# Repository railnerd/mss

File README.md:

Modular Signal System Boards
Copyright (c) 2012, Silicon Valley Lines Model Railroad Club

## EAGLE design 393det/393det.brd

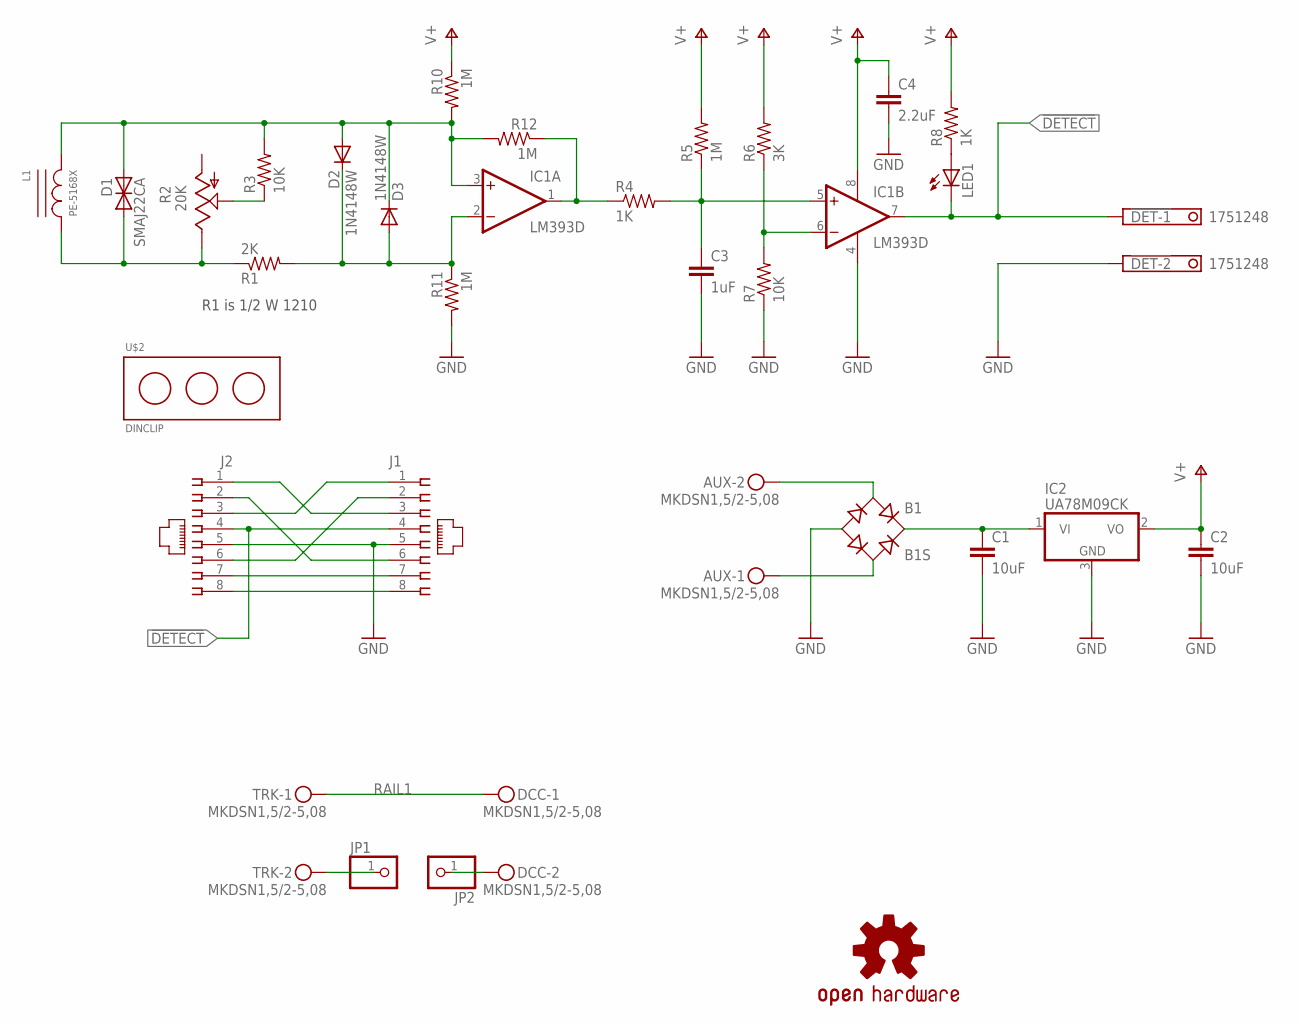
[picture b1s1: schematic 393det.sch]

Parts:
!DET: 1751248
AUX: MKDSN1,5/2-5,08
B1: B1S; MBS
C1, C2: 10uF; 1210
C3: 1uF; 0805
C4: 2.2uF; 0805
D1: SMAJ22CA; SMA
D2, D3: 1N4148W; SOD123
DCC: MKDSN1,5/2-5,08
IC1: LM393D; SO08
IC2: UA78M09CK; TO252
J1, J2: 215877-7
JP1, JP2: PINHD-1X1; 1X01
L1: PE-5168X
LED1: LED5MM
R1: 2K; R1206
R2: 20K; B25U
R3, R7: 10K; 0805
R4, R8: 1K; 0805
R5, R10, R11, R12: 1M; 0805
R6: 3K; 0805
TRK: MKDSN1,5/2-5,08
U$1: OSHW-LOGOM; OSHW-LOGO-M
U$2: DINCLIP; 1201578

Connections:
!DETECT: !DET.1, IC1.7 (OUT), J1.4, J2.4, LED1.K (C)
GND: !DET.2, B1.-, C1.2, C2.2, C3.2, C4.2, IC1.4 (V-), IC2.3 (GND), J1.5, J2.5, R7.1, R11.2
unnamed: D1.A (1), D2.A, D3.C, IC1.3 (+IN), L1.P$2, R3.2, R10.2, R12.2
unnamed: C3.1, IC1.5 (+IN), R4.2, R5.1
unnamed: D2.C, D3.A, IC1.2 (-IN), R1.2, R11.1
unnamed: D1.C (2), L1.P$1, R1.1, R2.E
unnamed: R2.S, R3.1
unnamed: LED1.A, R8.1
unnamed: AUX.2, B1.AC1
unnamed: AUX.1, B1.AC2
unnamed: J1.8, J2.8
unnamed: JP1.1, TRK.2
unnamed: DCC.2, JP2.1
unnamed: J1.7, J2.7
unnamed: IC1.1 (OUT), R4.1, R12.1
unnamed: IC1.6 (-IN), R6.1, R7.2
unnamed: J1.3, J2.1
unnamed: J1.1, J2.3
unnamed: J1.6, J2.2
unnamed: J1.2, J2.6
unnamed: B1.+, C1.1, IC2.1 (VI)
RAIL1: DCC.1, TRK.1
V+: C2.1, C4.1, IC1.8 (V+), IC2.2 (VO), R5.2, R6.2, R8.2, R10.1

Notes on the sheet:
R1 is 1/2 W 1210

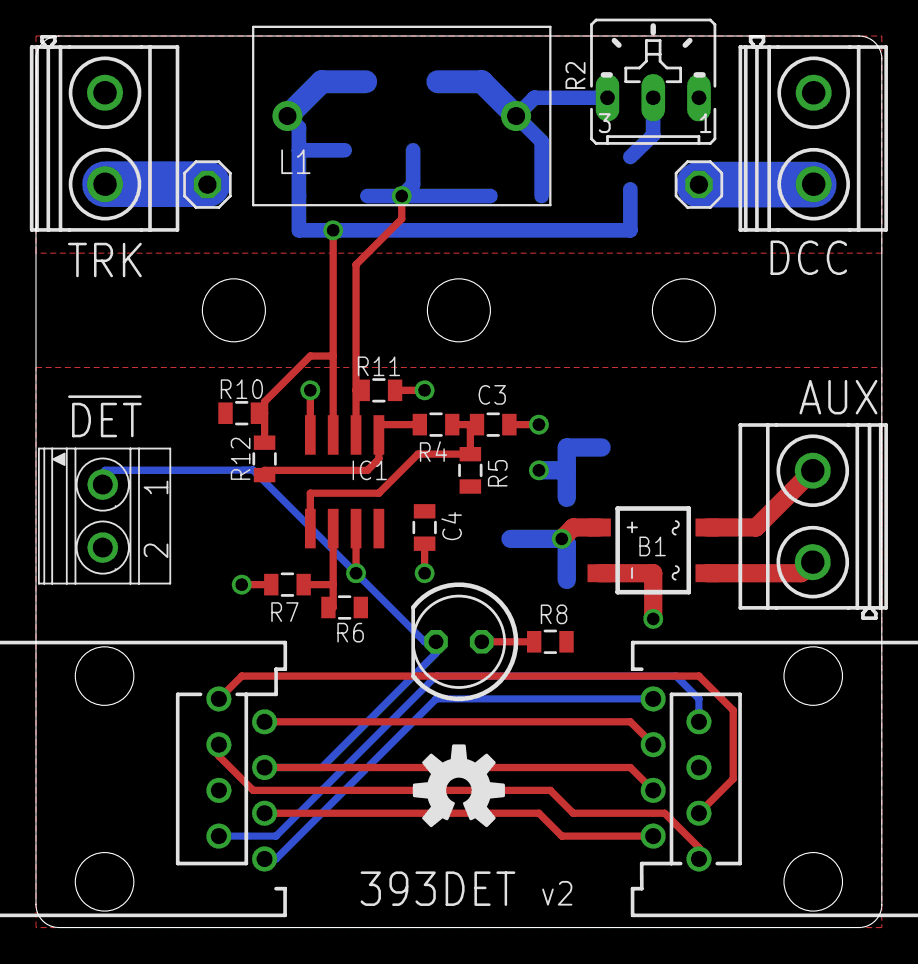
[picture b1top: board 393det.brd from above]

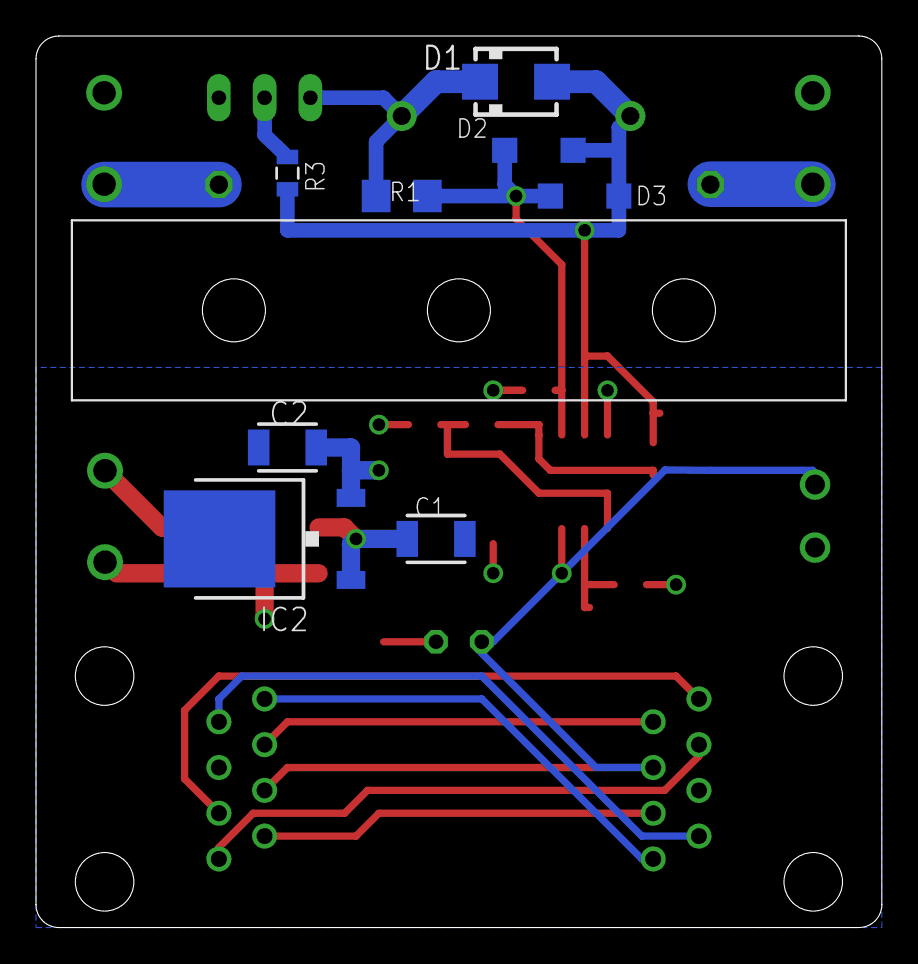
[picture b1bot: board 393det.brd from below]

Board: 2 copper layers, 47.0 x 49.5 mm, 33 parts (8 on the bottom side), 23 nets.

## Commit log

2012-02-27 kill some extra files
2012-02-27 round off the corners
2012-03-02 add 393det
2012-03-03 changes from review
2012-03-03 minor cleanup
2012-03-03 C1,C2: 1206->1210
2012-03-03 added VR
2012-03-03 minor layout fixes
2012-03-07 add resistors for input clamping and hysteresis
2012-04-14 v0.5: fix approach lighting, add power to opto connection
2012-06-03 tweaks for fab
2012-06-03 add generic cascade
2013-07-17 minor tweaks to get ready for fab.
